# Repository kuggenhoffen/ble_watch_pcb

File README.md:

# ble_watch_pcb
BLE Watch for HRM

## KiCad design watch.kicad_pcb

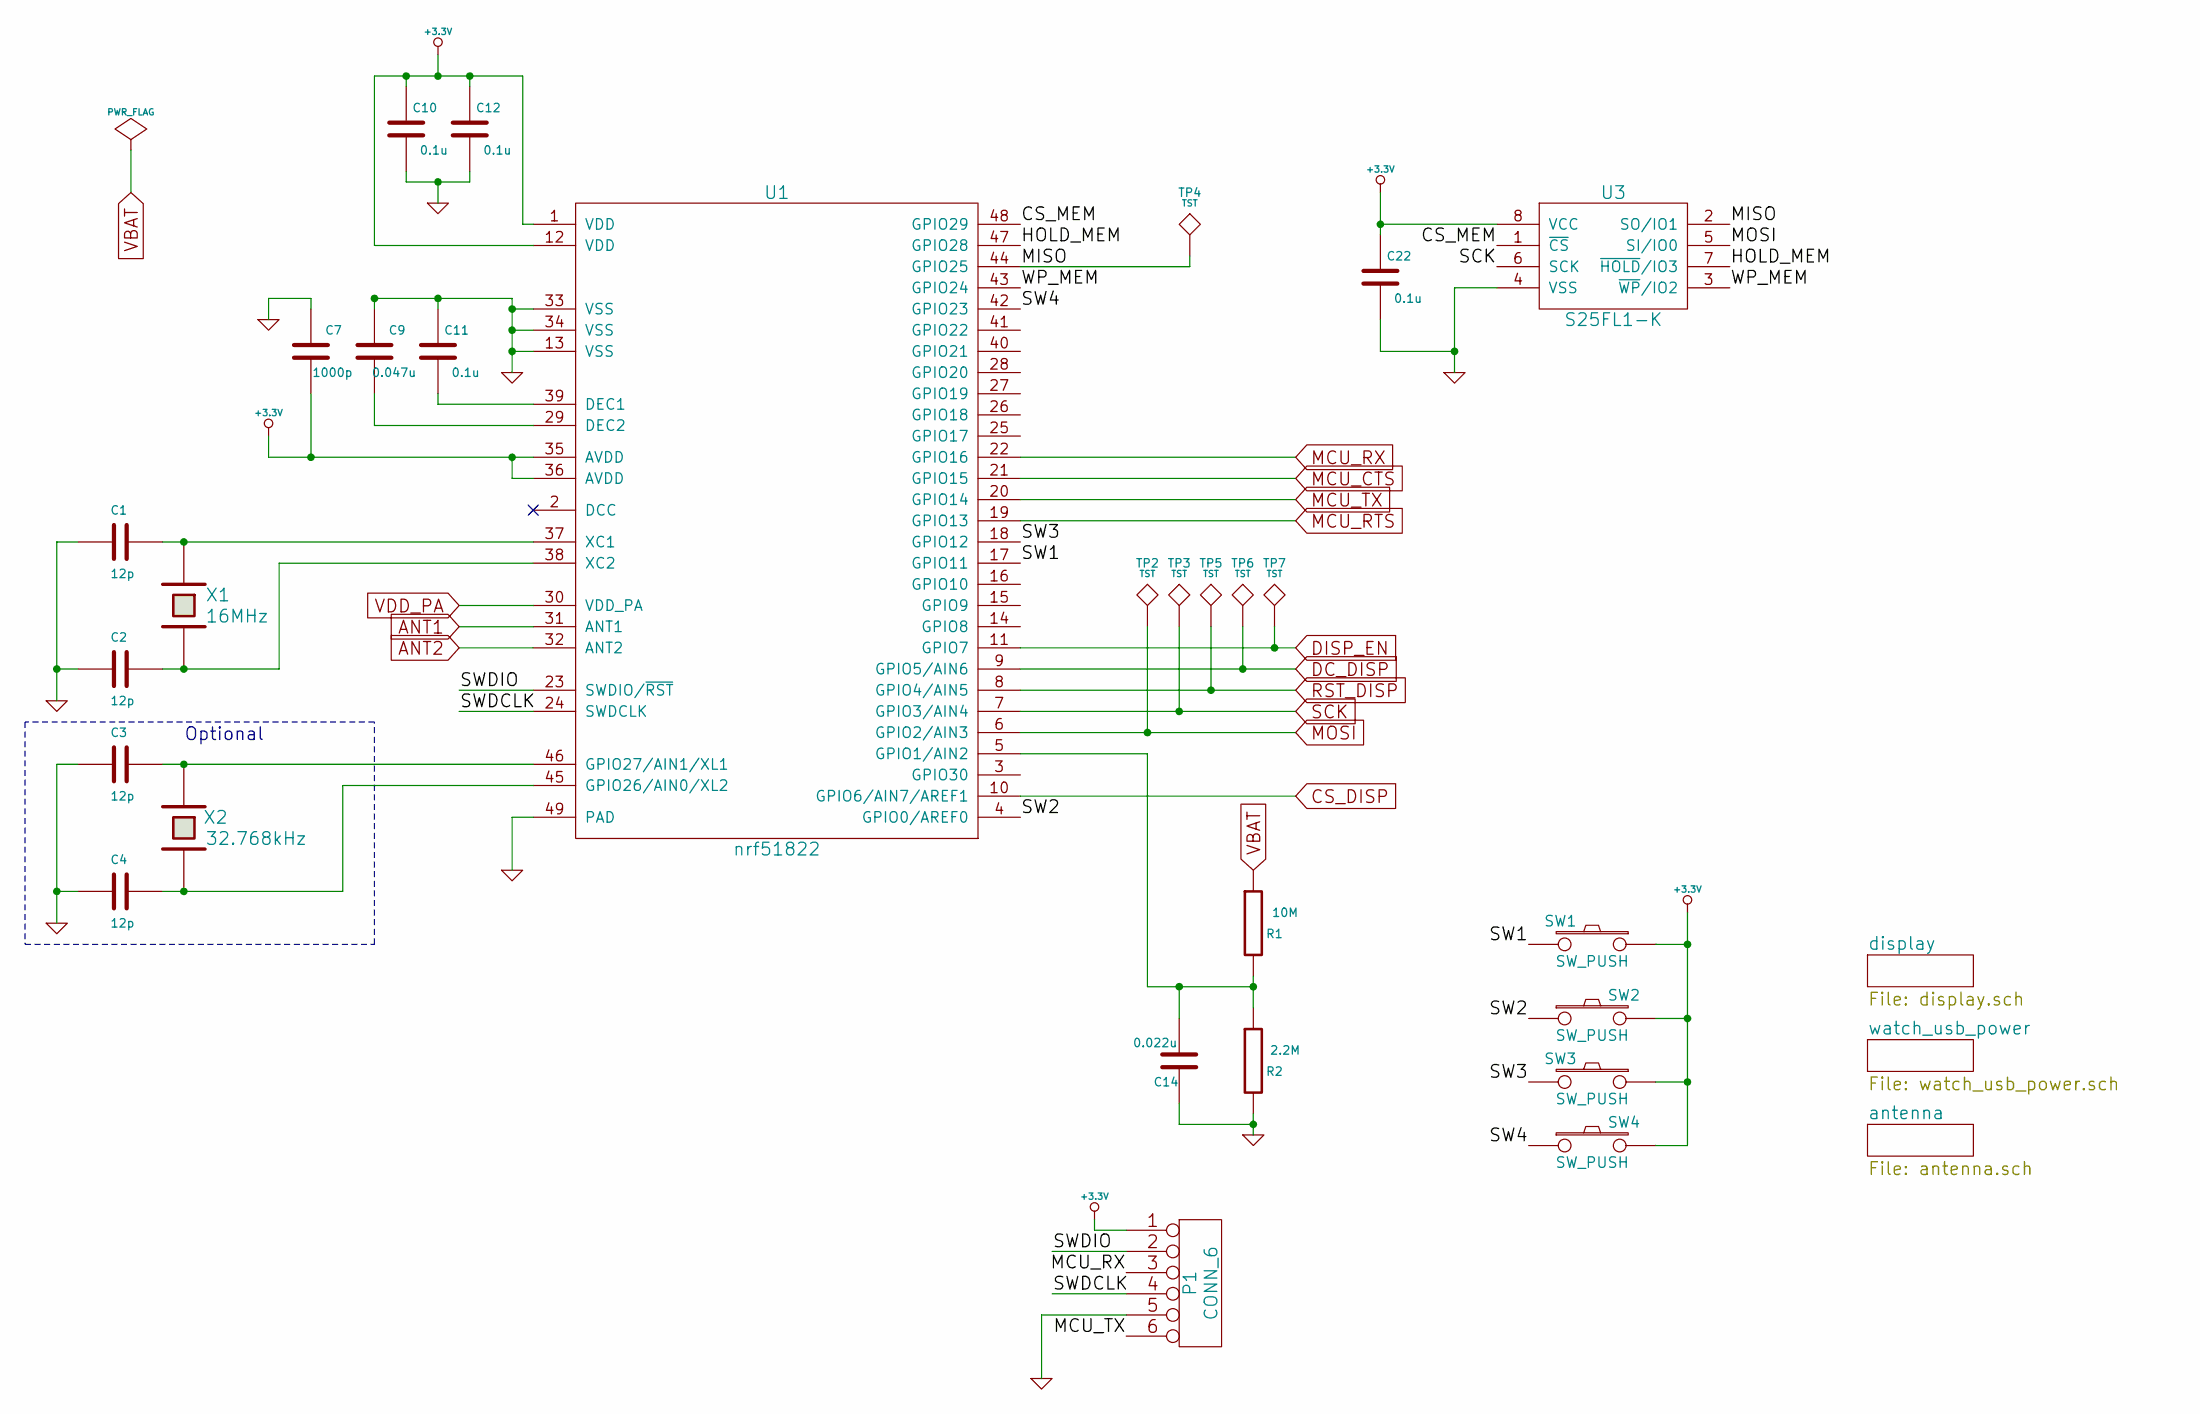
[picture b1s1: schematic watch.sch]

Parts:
C1, C2, C3, C4: 12p; SMD-0603
C7: 1000p; SMD-0603
C9: 0.047u; SMD-0603
C10, C11, C12, C22: 0.1u; SMD-0603
C14: 0.022u; SMD-0603
P1: CONN_6; TC2030-MCP-NL
R1: 10M; SMD-0603
R2: 2.2M; SMD-0603
SW1, SW2, SW3, SW4: SW_PUSH; SKTDLDE010
TP2, TP3, TP4, TP5, TP6, TP7: TST; Measurement_Point_Round-SMD-Pad_Small
U1: nrf51822; QFN-48-1EP_7x7mm_Pitch0.5mm
U3: S25FL1-K; SOIC-8-W
X1: 16MHz; CRYSTAL_SMD_2520_4PADS
X2: 32.768kHz; FC-135_SMD_CRYSTAL

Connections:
+3.3V: C7.1, C10.2, C12.2, C22.2, P1.1, SW1.1, SW2.2, SW3.1, SW4.2, U1.1 (VDD), U1.12 (VDD), U1.35 (AVDD), U1.36 (AVDD), U3.8 (VCC); also elsewhere on the board
/CS_MEM: U1.48 (GPIO29), U3.1 (~CS)
/HOLD_MEM: U1.47 (GPIO28), U3.7 (~HOLD~/IO3)
/MISO: TP4.1, U1.44 (GPIO25), U3.2 (SO/IO1)
/SW1: SW1.2, U1.17 (GPIO11)
/SW2: SW2.1, U1.4 (GPIO0/AREF0)
/SW3: SW3.2, U1.18 (GPIO12)
/SW4: SW4.1, U1.42 (GPIO23)
/SWDCLK: P1.4, U1.24 (SWDCLK)
/SWDIO: P1.2, U1.23 (SWDIO/~RST)
/WP_MEM: U1.43 (GPIO24), U3.3 (~WP~/IO2)
ANT1: U1.31 (ANT1); also elsewhere on the board
ANT2: U1.32 (ANT2); also elsewhere on the board
CS_DISP: U1.10 (GPIO6/AIN7/AREF1); also elsewhere on the board
DC_DISP: TP6.1, U1.9 (GPIO5/AIN6); also elsewhere on the board
DISP_EN: TP7.1, U1.11 (GPIO7); also elsewhere on the board
GND: C1.2, C2.2, C3.2, C4.2, C7.2, C9.2, C10.1, C11.2, C12.1, C14.1, C22.1, P1.5, R2.2, U1.13 (VSS), U1.33 (VSS), U1.34 (VSS), U1.49 (PAD), U3.4 (VSS); also elsewhere on the board
MCU_CTS: U1.21 (GPIO15); also elsewhere on the board
MCU_RTS: U1.19 (GPIO13); also elsewhere on the board
MCU_RX: P1.3, U1.22 (GPIO16); also elsewhere on the board
MCU_TX: P1.6, U1.20 (GPIO14); also elsewhere on the board
MOSI: TP2.1, U1.6 (GPIO2/AIN3), U3.5 (SI/IO0); also elsewhere on the board
unnamed: C1.1, U1.37 (XC1), X1.1
unnamed: C2.1, U1.38 (XC2), X1.3 (2)
unnamed: C3.1, U1.46 (GPIO27/AIN1/XL1), X2.1
unnamed: C4.1, U1.45 (GPIO26/AIN0/XL2), X2.2
unnamed: C9.1, U1.29 (DEC2)
unnamed: C11.1, U1.39 (DEC1)
unnamed: C14.2, R1.2, R2.1, U1.5 (GPIO1/AIN2)
RST_DISP: TP5.1, U1.8 (GPIO4/AIN5); also elsewhere on the board
SCK: TP3.1, U1.7 (GPIO3/AIN4), U3.6 (SCK); also elsewhere on the board
VBAT: R1.1; also elsewhere on the board
VDD_PA: U1.30 (VDD_PA); also elsewhere on the board

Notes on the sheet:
Optional

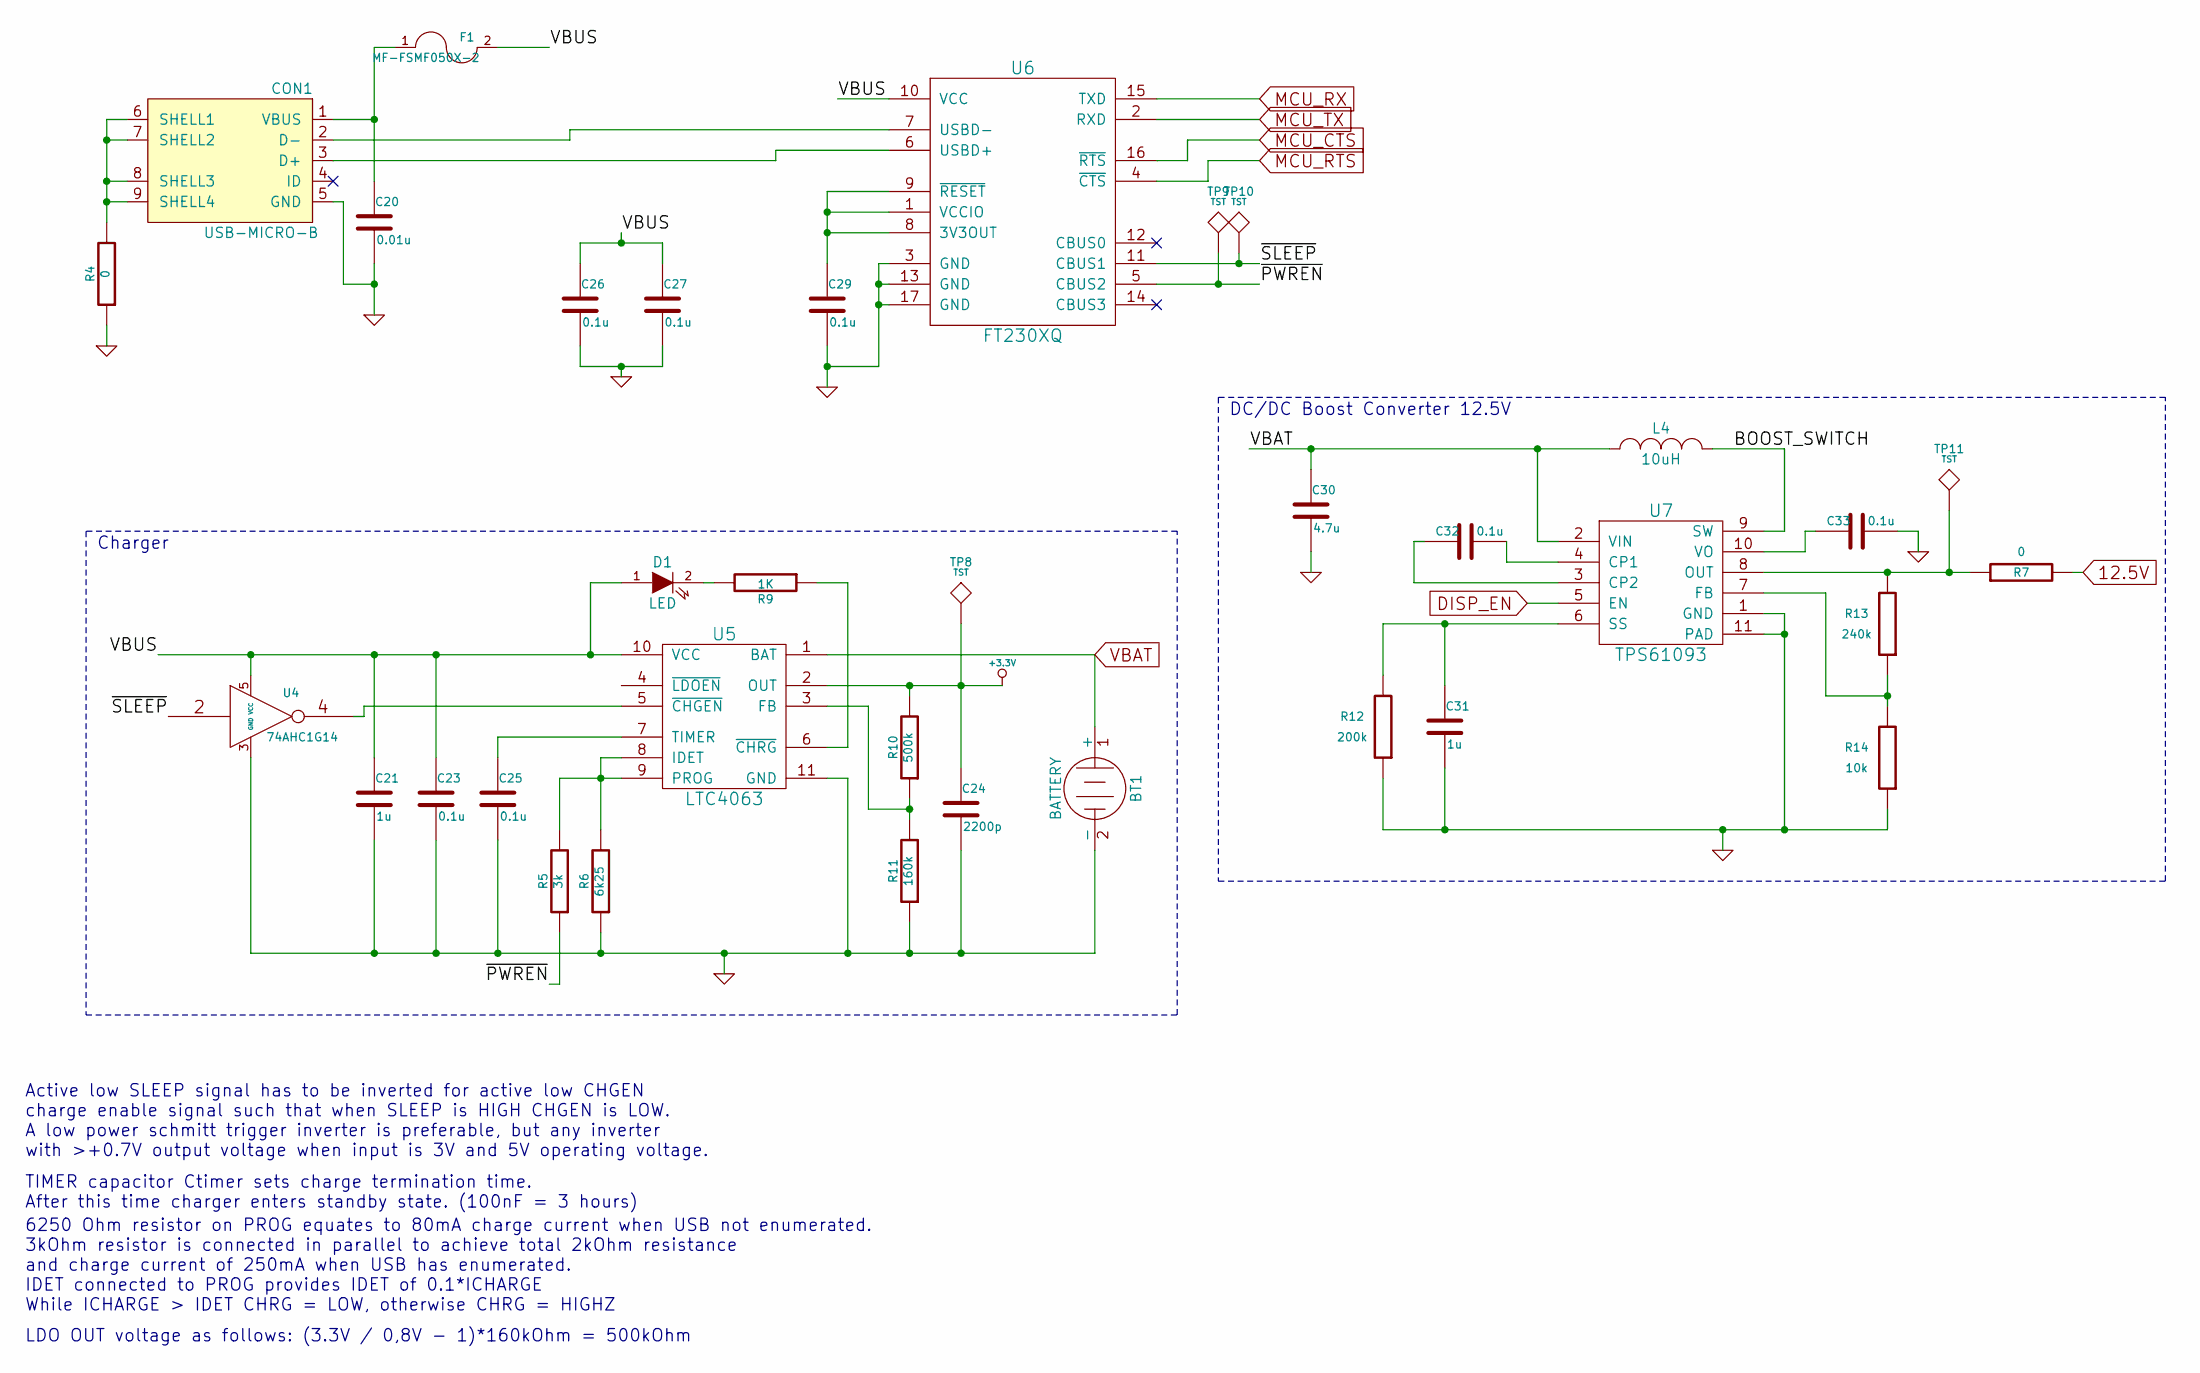
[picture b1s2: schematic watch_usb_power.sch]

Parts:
BT1: BATTERY; SMD-1210
C20: 0.01u; SMD-0603
C21, C31: 1u; SMD-0603
C23, C25, C26, C27, C29, C32, C33: 0.1u; SMD-0603
C24: 2200p; SMD-0603
C30: 4.7u; SMD-0603
CON1: USB-MICRO-B; USB_MICRO_B_FEMALE_MIDMOUNT
D1: LED; LED-0603
F1: MF-FSMF050X-2; SMD-0603
L4: 10uH; 4012-Metric-Handsolder
R4, R7: 0; SMD-0603
R5: 3k; SMD-0603
R6: 6k25; SMD-0603
R9: 1K; SMD-0603
R10: 500k; SMD-0603
R11: 160k; SMD-0603
R12: 200k; SMD-0603
R13: 240k; SMD-0603
R14: 10k; SMD-0603
TP8, TP9, TP10, TP11: TST; Measurement_Point_Round-SMD-Pad_Small
U4: 74AHC1G14; SOT-353
U5: LTC4063; DFN-10-1EP_3x3mm_Pitch0.5mm
U6: FT230XQ; QFN-16-1EP_3x3mm_Pitch0.5mm
U7: TPS61093; SON-10-1EP_2.6x2.6mm_Pitch0.5mm

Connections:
12.5V: R7.2; also elsewhere on the board
+3.3V: C24.1, R10.2, TP8.1, U5.2 (OUT); also elsewhere on the board
/watch_usb_power/BOOST_SWITCH: L4.2, U7.9 (SW)
/watch_usb_power/VBUS: C21.1, C23.1, C26.1, C27.1, D1.1 (A), F1.2, U4.5 (VCC), U5.10 (VCC), U6.10 (VCC)
/watch_usb_power/~PWREN: R5.1, TP9.1, U6.5 (CBUS2)
/watch_usb_power/~SLEEP: TP10.1, U4.2, U6.11 (CBUS1)
DISP_EN: U7.5 (EN); also elsewhere on the board
GND: BT1.2 (-), C20.2, C21.2, C23.2, C24.2, C25.2, C26.2, C27.2, C29.2, C30.2, C31.2, C33.1, CON1.5 (GND), R4.1, R6.1, R11.1, R12.1, R14.1, U4.3 (GND), U5.11 (GND), U6.3 (GND), U6.13 (GND), U6.17 (GND), U7.1 (GND), U7.11 (PAD); also elsewhere on the board
MCU_CTS: U6.16 (~RTS); also elsewhere on the board
MCU_RTS: U6.4 (~CTS); also elsewhere on the board
MCU_RX: U6.15 (TXD); also elsewhere on the board
MCU_TX: U6.2 (RXD); also elsewhere on the board
unnamed: C20.1, CON1.1 (VBUS), F1.1
unnamed: C25.1, U5.7 (TIMER)
unnamed: C29.1, U6.1 (VCCIO), U6.8 (3V3OUT), U6.9 (~RESET)
unnamed: C31.1, R12.2, U7.6 (SS)
unnamed: C32.1, U7.4 (CP1)
unnamed: C32.2, U7.3 (CP2)
unnamed: C33.2, U7.10 (VO)
unnamed: CON1.2 (D-), U6.7 (USBD-)
unnamed: CON1.3 (D+), U6.6 (USBD+)
unnamed: CON1.6 (SHELL1), CON1.7 (SHELL2), CON1.8 (SHELL3), CON1.9 (SHELL4), R4.2
unnamed: D1.2 (K), R9.2
unnamed: R5.2, R6.2, U5.8 (IDET), U5.9 (PROG)
unnamed: R9.1, U5.6 (~CHRG)
unnamed: R10.1, R11.2, U5.3 (FB)
unnamed: R13.1, R14.2, U7.7 (FB)
unnamed: R7.1, R13.2, TP11.1, U7.8 (OUT)
unnamed: U4.4, U5.5 (~CHGEN)
VBAT: BT1.1 (+), C30.1, L4.1, U5.1 (BAT), U7.2 (VIN); also elsewhere on the board

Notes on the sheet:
TIMER capacitor Ctimer sets charge termination time. After this time charger enters standby state. (100nF = 3 hours)
6250 Ohm resistor on PROG equates to 80mA charge current when USB not enumerated. 3kOhm resistor is connected in parallel to achieve total 2kOhm resistance and charge current of 250mA when USB has enumerated. IDET connected to PROG provides IDET of 0.1*ICHARGE While ICHARGE > IDET CHRG = LOW, other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
LDO OUT voltage as follows: (3.3V / 0,8V - 1)*160kOhm = 500kOhm
Charger
Active low SLEEP signal has to be inverted for active low CHGEN charge enable signal such that when SLEEP is HIGH CHGEN is LOW. A low power schmitt trigger inverter is preferable, but any inverter with >+0.7V output voltage when input is 3V and 5V operating voltage.
DC/DC Boost Converter 12.5V

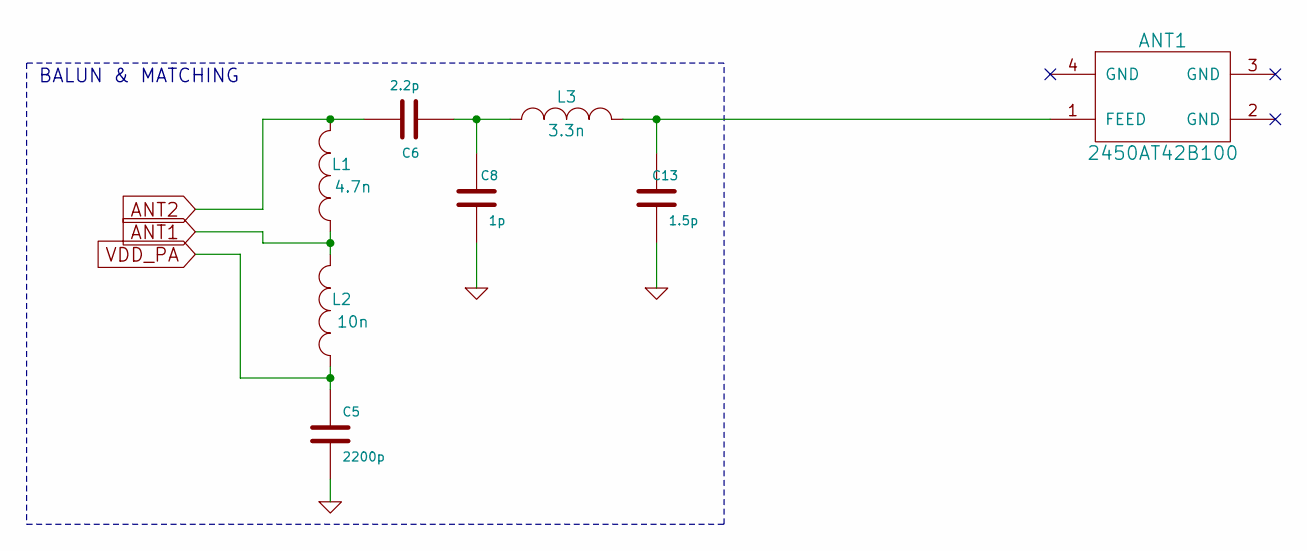
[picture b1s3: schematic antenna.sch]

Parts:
ANT1: 2450AT42B100; ANTENNA_2.4GHz_SMD_2450AT42B100
C5: 2200p; SMD-0402
C6: 2.2p; SMD-0402
C8: 1p; SMD-0402
C13: 1.5p; SMD-0402
L1: 4.7n; SMD-0402
L2: 10n; SMD-0402
L3: 3.3n; SMD-0402

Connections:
ANT1: L1.1, L2.2; also elsewhere on the board
ANT2: C6.1, L1.2; also elsewhere on the board
GND: C5.2, C8.1, C13.1; also elsewhere on the board
unnamed: ANT1.1 (FEED), C13.2, L3.2
unnamed: C6.2, C8.2, L3.1
VDD_PA: C5.1, L2.1; also elsewhere on the board

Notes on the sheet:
BALUN & MATCHING

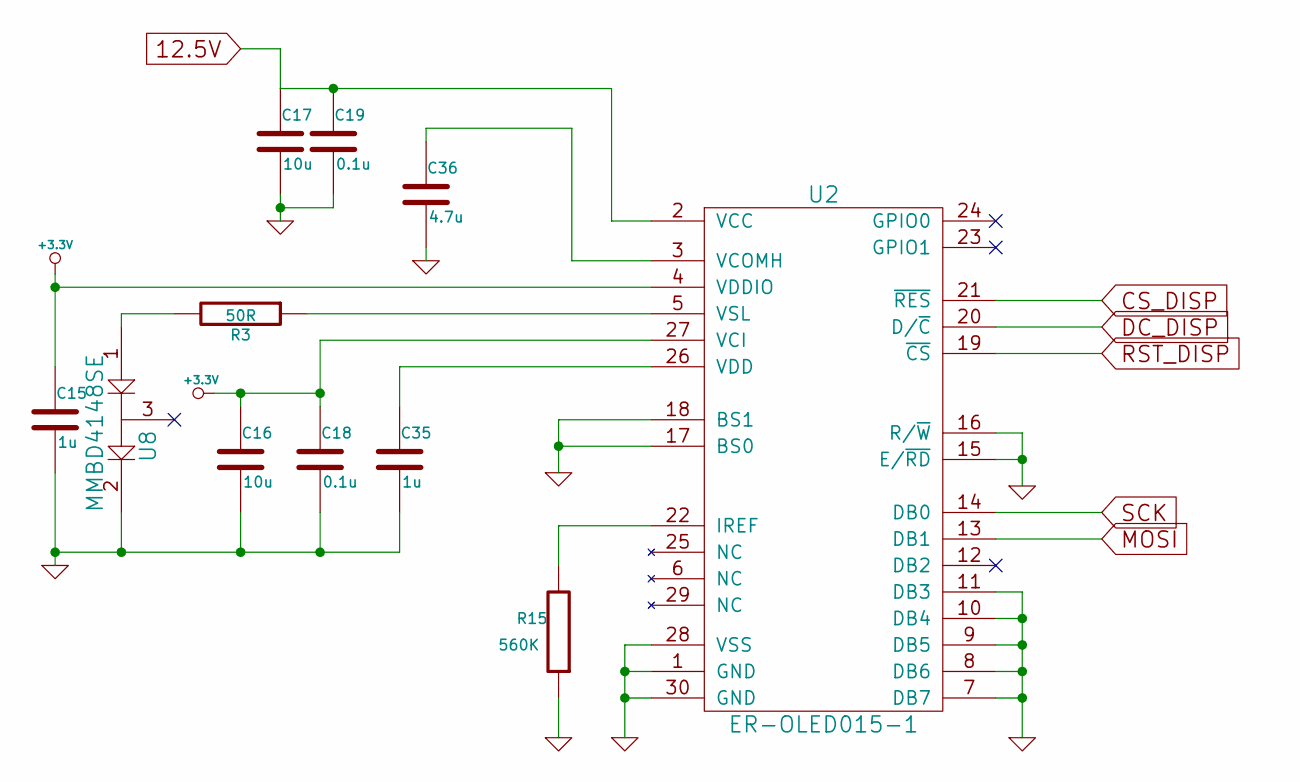
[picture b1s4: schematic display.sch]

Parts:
C15, C35: 1u; SMD-0603
C16, C17: 10u; SMD-0603
C18, C19: 0.1u; SMD-0603
C36: 4.7u; SMD-0603
R3: 50R; SMD-0603
R15: 560K; SMD-0603
U2: ER-OLED015-1; ER-OLED-CON30-BOTTOM-CONTACT
U8: MMBD4148SE; SOT-23

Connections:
12.5V: C17.1, C19.1, U2.2 (VCC); also elsewhere on the board
+3.3V: C15.1, C16.1, C18.1, U2.4 (VDDIO), U2.27 (VCI); also elsewhere on the board
CS_DISP: U2.21 (~RES); also elsewhere on the board
DC_DISP: U2.20 (D/~C); also elsewhere on the board
GND: C15.2, C16.2, C17.2, C18.2, C19.2, C35.2, C36.2, R15.1, U2.1 (GND), U2.7 (DB7), U2.8 (DB6), U2.9 (DB5), U2.10 (DB4), U2.11 (DB3), U2.15 (E/~RD), U2.16 (R/~W), U2.17 (BS0), U2.18 (BS1), U2.28 (VSS), U2.30 (GND), U8.2; also elsewhere on the board
MOSI: U2.13 (DB1); also elsewhere on the board
unnamed: C35.1, U2.26 (VDD)
unnamed: C36.1, U2.3 (VCOMH)
unnamed: R3.1, U2.5 (VSL)
unnamed: R3.2, U8.1
unnamed: R15.2, U2.22 (IREF)
RST_DISP: U2.19 (~CS); also elsewhere on the board
SCK: U2.14 (DB0); also elsewhere on the board

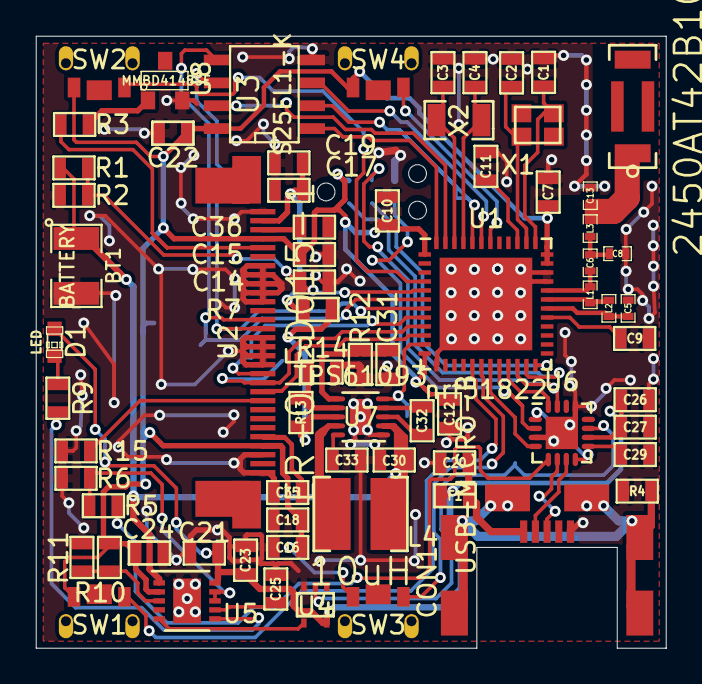
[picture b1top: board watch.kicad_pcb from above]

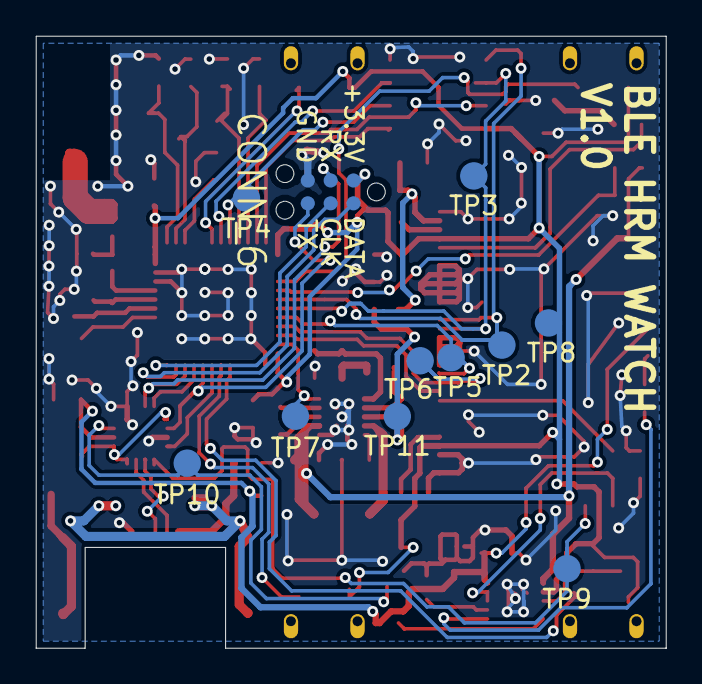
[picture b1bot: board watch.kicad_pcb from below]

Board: 2 copper layers, 35.0 x 34.0 mm, 82 parts (11 on the bottom side), 62 nets.

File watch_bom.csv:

Reference, Value, Footprint, Datasheet
U1,nrf51822,Housings_DFN_QFN:QFN-48-1EP_7x7mm_Pitch0.5mm,
C1,12pF,SMD_Packages:SMD-0603,
C2,12pF,SMD_Packages:SMD-0603,
C12,100nF,SMD_Packages:SMD-0603,
C10,100nF,SMD_Packages:SMD-0603,
C11,100nF,SMD_Packages:SMD-0603,
C9,47nF,SMD_Packages:SMD-0603,
C7,1nF,SMD_Packages:SMD-0603,
X2,32.768kHz,Omat:FC-135_SMD_CRYSTAL,
C3,12pF,SMD_Packages:SMD-0603,
C4,12pF,SMD_Packages:SMD-0603,
U3,S25FL1-K,SMD_Packages:SOIC-8-W,
SW1,SW_PUSH,Omat:SKTDLDE010,
SW2,SW_PUSH,Omat:SKTDLDE010,
SW3,SW_PUSH,Omat:SKTDLDE010,
SW4,SW_PUSH,Omat:SKTDLDE010,
R1,10M,SMD_Packages:SMD-0603,
R2,2.2M,SMD_Packages:SMD-0603,
C14,22nF,SMD_Packages:SMD-0603,
P1,CONN_6,Omat:TC2030-MCP-NL,
X1,16MHz,Omat:CRYSTAL_SMD_2520_4PADS,
C22,100nF,SMD_Packages:SMD-0603,
TP7,TST,Measurement_Points:Measurement_Point_Round-SMD-Pad_Small,
TP6,TST,Measurement_Points:Measurement_Point_Round-SMD-Pad_Small,
TP5,TST,Measurement_Points:Measurement_Point_Round-SMD-Pad_Small,
TP3,TST,Measurement_Points:Measurement_Point_Round-SMD-Pad_Small,
TP2,TST,Measurement_Points:Measurement_Point_Round-SMD-Pad_Small,
TP4,TST,Measurement_Points:Measurement_Point_Round-SMD-Pad_Small,
U5,LTC4063,Housings_DFN_QFN:DFN-10-1EP_3x3mm_Pitch0.5mm,
CON1,USB-MICRO-B,Omat:USB_MICRO_B_FEMALE_MIDMOUNT,
F1,MF-FSMF050X-2,SMD_Packages:SMD-0603,
R4,0,SMD_Packages:SMD-0603,
C20,10nF,SMD_Packages:SMD-0603,
C29,100nF,SMD_Packages:SMD-0603,
C26,100nF,SMD_Packages:SMD-0603,
C27,4.7uF,SMD_Packages:SMD-0603,
C23,100nF,SMD_Packages:SMD-0603,
D1,LED,LEDs:LED-0603,
C25,100nF,SMD_Packages:SMD-0603,
R6,6k25,SMD_Packages:SMD-0603,
R9,1K,SMD_Packages:SMD-0603,
C21,1uF,SMD_Packages:SMD-0603,
BT1,BATTERY,SMD_Packages:SMD-1210,
R11,160k,SMD_Packages:SMD-0603,
R10,500k,SMD_Packages:SMD-0603,
U4,74AHC1G14,SMD_Packages:SOT-353,
R5,3k,SMD_Packages:SMD-0603,
U7,TPS61093,Omat:SON-10-1EP_2.6x2.6mm_Pitch0.5mm,
C30,4.7uF,SMD_Packages:SMD-0603,
L4,10uH,Omat:4012-Metric-Handsolder,
C32,100nF,SMD_Packages:SMD-0603,
C31,1uF,SMD_Packages:SMD-0603,
R12,200k,SMD_Packages:SMD-0603,
C33,100nF,SMD_Packages:SMD-0603,
R13,240k,SMD_Packages:SMD-0603,
R14,10k,SMD_Packages:SMD-0603,
U6,FT230XQ,Housings_DFN_QFN:QFN-16-1EP_3x3mm_Pitch0.5mm,
TP10,TST,Measurement_Points:Measurement_Point_Round-SMD-Pad_Small,
TP9,TST,Measurement_Points:Measurement_Point_Round-SMD-Pad_Small,
TP8,TST,Measurement_Points:Measurement_Point_Round-SMD-Pad_Small,
TP11,TST,Measurement_Points:Measurement_Point_Round-SMD-Pad_Small,
R7,0,SMD_Packages:SMD-0603,
ANT1,2450AT42B100,Omat:ANTENNA_2.4GHz_SMD_2450AT42B100,
L1,4.7nH,SMD_Packages:SMD-0402,
L2,10nH,SMD_Packages:SMD-0402,
C5,2.2nF,SMD_Packages:SMD-0402,
C6,2.2pF,SMD_Packages:SMD-0402,
C8,1pF,SMD_Packages:SMD-0402,
L3,3.3nH,SMD_Packages:SMD-0402,
C13,1.5pF,SMD_Packages:SMD-0402,
U2,ER-OLED015-1,Omat:ER-OLED-CON30-BOTTOM-CONTACT,
C17,10u,SMD_Packages:SMD-0603,
C19,100n,SMD_Packages:SMD-0603,
C36,4.7u,SMD_Packages:SMD-0603,
C15,1u,SMD_Packages:SMD-0603,
R3,50R,SMD_Packages:SMD-0603,
C18,100n,SMD_Packages:SMD-0603,
C16,10u,SMD_Packages:SMD-0603,
C35,1u,SMD_Packages:SMD-0603,
R15,560K,SMD_Packages:SMD-0603,
U8,MMBD4148SE,SMD_Packages:SOT-23,

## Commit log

2016-01-31 Fixed footprints for MCU and USB-UART, added testpoints
2016-01-31 Updated sheet info, added schematic, board PDF and BOM
2016-01-31 Added .gitignore, finished midmount layout
2016-01-31 Minor modifications
2016-01-31 Test thermal pad area
2016-01-31 Added pcb errata file
2016-01-31 Added missing 2.2uF cap to LTC4063 LDO output, normalized capacitor values to micro and pico, removed units from component values
2016-01-31 Changed gerber output options
2016-01-31 Added testpoints, adjusted silkscreen texts
